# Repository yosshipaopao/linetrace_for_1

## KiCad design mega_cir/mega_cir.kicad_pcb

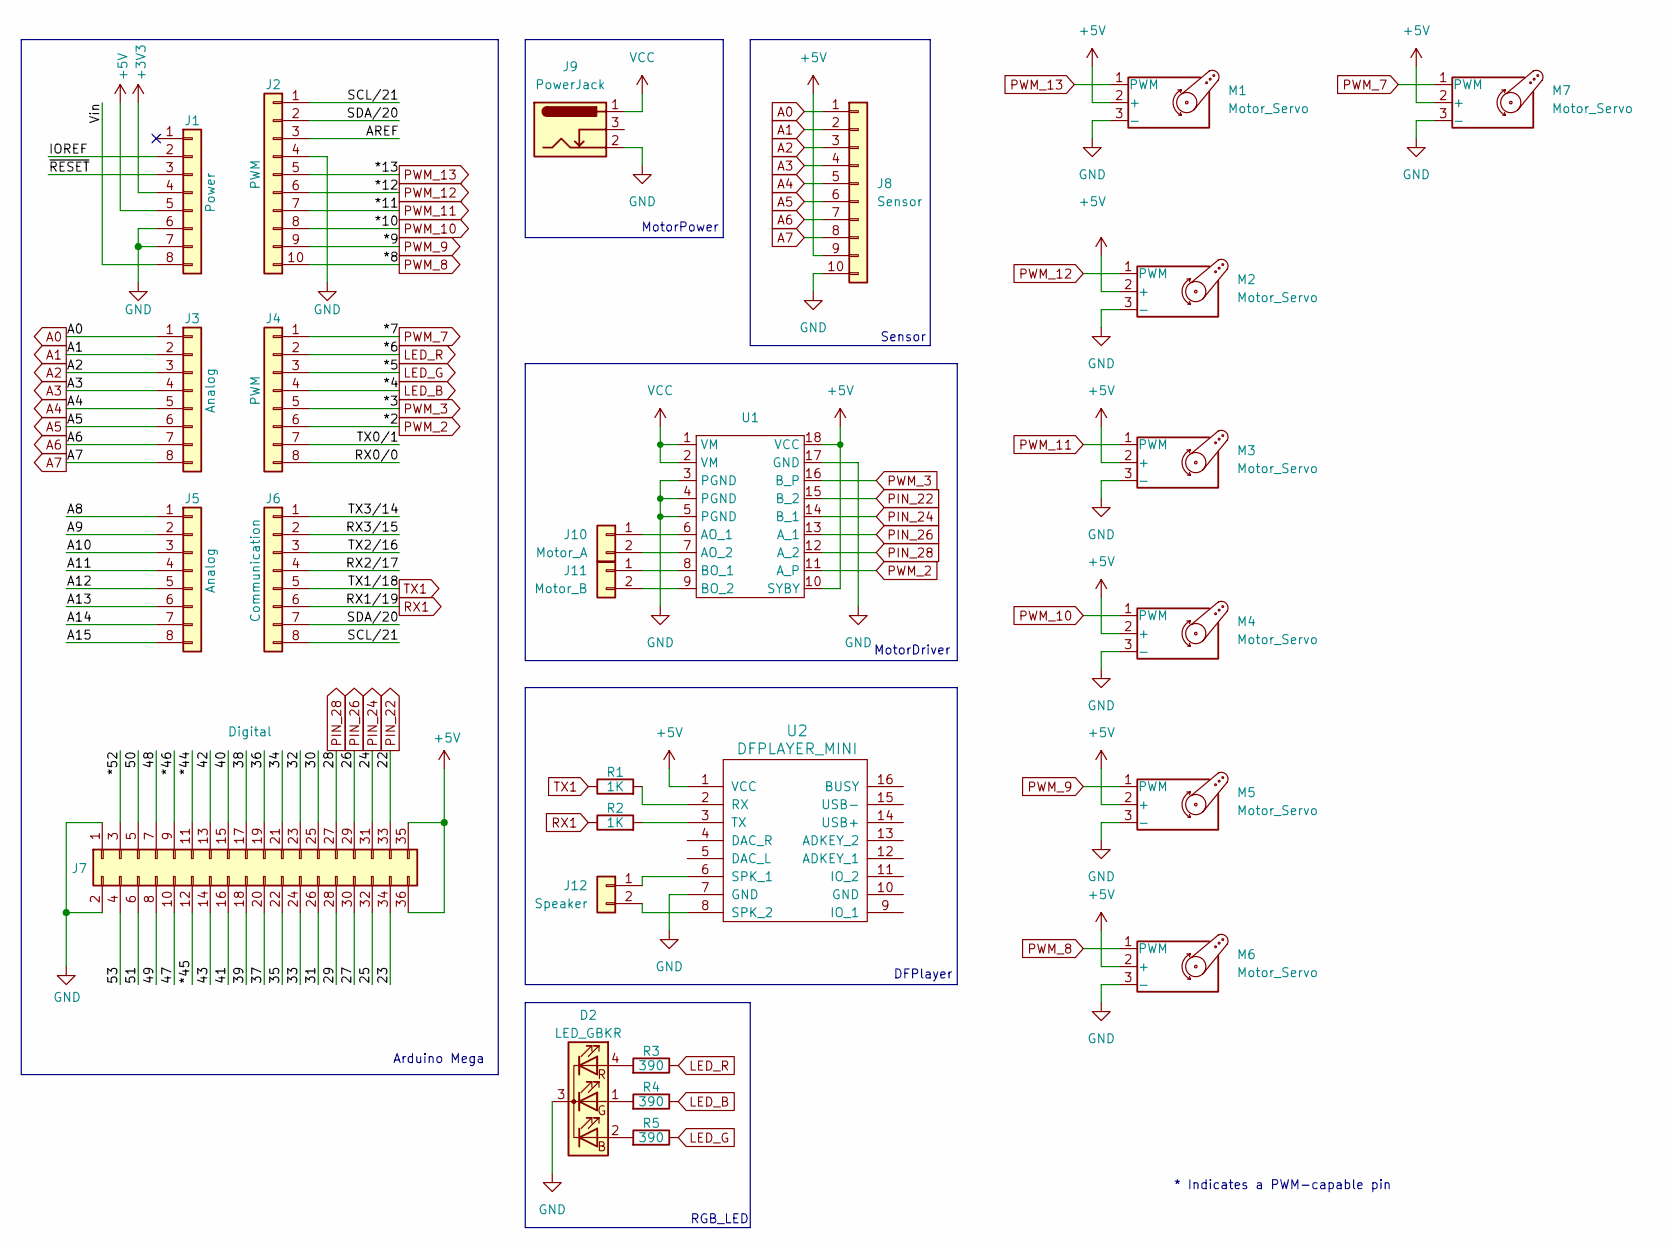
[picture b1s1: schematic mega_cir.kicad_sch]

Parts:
D2: LED_GBKR; PinHeader_1x04_P2.54mm_Vertical
J1: Power; PinSocket_1x08_P2.54mm_Vertical
J2: PWM; PinSocket_1x10_P2.54mm_Vertical
J3, J5: Analog; PinSocket_1x08_P2.54mm_Vertical
J4: PWM; PinSocket_1x08_P2.54mm_Vertical
J6: Communication; PinSocket_1x08_P2.54mm_Vertical
J7: Digital; PinSocket_2x18_P2.54mm_Vertical
J8: Sensor; PinSocket_1x10_P2.54mm_Vertical
J9: PowerJack; BarrelJack_Horizontal
J10: Motor_A; PinSocket_1x02_P2.54mm_Vertical
J11: Motor_B; PinSocket_1x02_P2.54mm_Vertical
J12: Speaker; PinSocket_1x02_P2.54mm_Vertical
M1, M2, M3, M4, M5, M6, M7: Motor_Servo; PinHeader_1x03_P2.54mm_Vertical
R1, R2: 1K; R_Axial_DIN0207_L6.3mm_D2.5mm_P7.62mm_Horizontal
R3, R4, R5: 390; R_Axial_DIN0207_L6.3mm_D2.5mm_P7.62mm_Horizontal
U1: TB6612
U2: DFPLAYER_MINI; DFPlayer_mini

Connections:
+3V3: J1.4
+5V: J1.5, J7.35, J7.36, J8.9, M1.2 (+), M2.2 (+), M3.2 (+), M4.2 (+), M5.2 (+), M6.2 (+), M7.2 (+), U1.10 (SYBY), U1.18 (VCC), U2.1 (VCC)
/23: J7.34
/25: J7.32
/27: J7.30
/29: J7.28
/30: J7.25
/31: J7.26
/32: J7.23
/33: J7.24
/34: J7.21
/35: J7.22
/36: J7.19
/37: J7.20
/38: J7.17
/39: J7.18
/40: J7.15
/41: J7.16
/42: J7.13
/43: J7.14
/47: J7.10
/48: J7.7
/49: J7.8
/50: J7.5
/51: J7.6
/53: J7.4
/*44: J7.11
/*45: J7.12
/*46: J7.9
/*52: J7.3
/A8: J5.1
/A9: J5.2
/A10: J5.3
/A11: J5.4
/A12: J5.5
/A13: J5.6
/A14: J5.7
/A15: J5.8
/AREF: J2.3
/IOREF: J1.2
/RX0/0: J4.8
/RX2/17: J6.4
/RX3/15: J6.2
/SCL/21: J2.1, J6.8
/SDA/20: J2.2, J6.7
/TX0/1: J4.7
/TX2/16: J6.3
/TX3/14: J6.1
/Vin: J1.8
/~RESET: J1.3
A0: J3.1, J8.1
A1: J3.2, J8.2
A2: J3.3, J8.3
A3: J3.4, J8.4
A4: J3.5, J8.5
A5: J3.6, J8.6
A6: J3.7, J8.7
A7: J3.8, J8.8
GND: D2.3 (K), J1.6, J1.7, J2.4, J7.1, J7.2, J8.10, J9.2, M1.3 (-), M2.3 (-), M3.3 (-), M4.3 (-), M5.3 (-), M6.3 (-), M7.3 (-), U1.3 (PGND), U1.4 (PGND), U1.5 (PGND), U1.17 (GND), U2.7 (GND)
LED_B: J4.4, R4.1
LED_G: J4.3, R5.1
LED_R: J4.2, R3.1
unnamed: D2.2 (BA), R5.2
unnamed: D2.1 (GA), R4.2
unnamed: D2.4 (RA), R3.2
unnamed: J10.1, U1.6 (AO_1)
unnamed: J10.2, U1.7 (AO_2)
unnamed: J11.1, U1.8 (BO_1)
unnamed: J11.2, U1.9 (BO_2)
unnamed: J12.1, U2.6 (SPK_1)
unnamed: J12.2, U2.8 (SPK_2)
unnamed: R1.2, U2.2 (RX)
unnamed: R2.2, U2.3 (TX)
PIN_22: J7.33, U1.15 (B_2)
PIN_24: J7.31, U1.14 (B_1)
PIN_26: J7.29, U1.13 (A_1)
PIN_28: J7.27, U1.12 (A_2)
PWM_2: J4.6, U1.11 (A_P)
PWM_3: J4.5, U1.16 (B_P)
PWM_7: J4.1, M7.1 (PWM)
PWM_8: J2.10, M6.1 (PWM)
PWM_9: J2.9, M5.1 (PWM)
PWM_10: J2.8, M4.1 (PWM)
PWM_11: J2.7, M3.1 (PWM)
PWM_12: J2.6, M2.1 (PWM)
PWM_13: J2.5, M1.1 (PWM)
RX1: J6.6, R2.1
TX1: J6.5, R1.1
VCC: J9.1, U1.1 (VM), U1.2 (VM)

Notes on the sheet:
MotorDriver
Sensor
Arduino Mega
RGB_LED
* Indicates a PWM-capable pin
DFPlayer
MotorPower

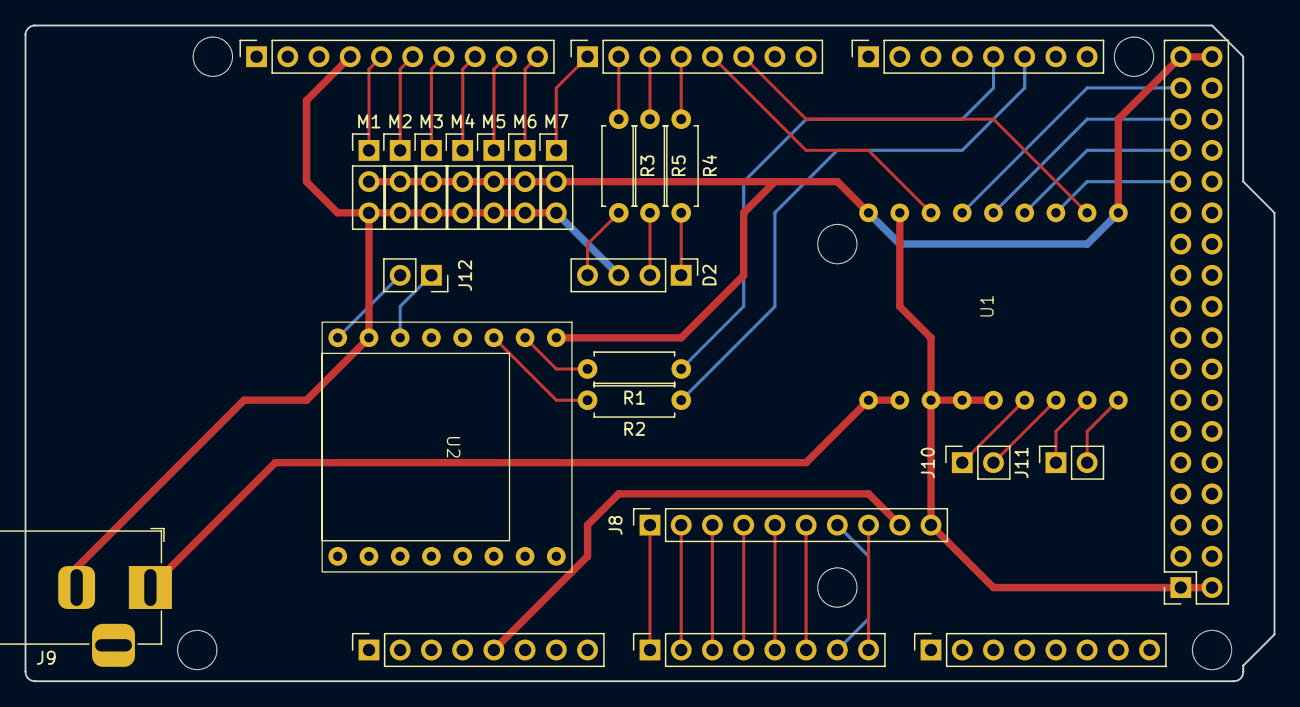
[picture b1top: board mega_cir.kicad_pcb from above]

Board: 2 copper layers, 101.6 x 53.3 mm, 33 parts (0 on the bottom side), 42 nets.

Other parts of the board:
MH1, MH2, MH3, MH4, MH5, MH6: MountingHole_3.2mm

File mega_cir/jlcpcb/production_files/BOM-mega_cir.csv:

Comment,Designator,Footprint,LCSC
LED_GBKR,D2,PinHeader_1x04_P2.54mm_Vertical,
DFPLAYER_MINI,U2,DFPlayer_mini,
~,U1,TB6612,
390,R5,R_Axial_DIN0207_L6.3mm_D2.5mm_P7.62mm_Horizontal,
390,R4,R_Axial_DIN0207_L6.3mm_D2.5mm_P7.62mm_Horizontal,
390,R3,R_Axial_DIN0207_L6.3mm_D2.5mm_P7.62mm_Horizontal,
1K,R2,R_Axial_DIN0207_L6.3mm_D2.5mm_P7.62mm_Horizontal,
1K,R1,R_Axial_DIN0207_L6.3mm_D2.5mm_P7.62mm_Horizontal,
Motor_Servo,M7,PinHeader_1x03_P2.54mm_Vertical,
Motor_Servo,M6,PinHeader_1x03_P2.54mm_Vertical,
Motor_Servo,M5,PinHeader_1x03_P2.54mm_Vertical,
Motor_Servo,M4,PinHeader_1x03_P2.54mm_Vertical,
Motor_Servo,M3,PinHeader_1x03_P2.54mm_Vertical,
Motor_Servo,M2,PinHeader_1x03_P2.54mm_Vertical,
Motor_Servo,M1,PinHeader_1x03_P2.54mm_Vertical,
Speaker,J12,PinSocket_1x02_P2.54mm_Vertical,
Motor_B,J11,PinSocket_1x02_P2.54mm_Vertical,
Motor_A,J10,PinSocket_1x02_P2.54mm_Vertical,
PowerJack,J9,BarrelJack_Horizontal,
Sensor,J8,PinSocket_1x10_P2.54mm_Vertical,
Digital,J7,PinSocket_2x18_P2.54mm_Vertical,
Power,J1,PinSocket_1x08_P2.54mm_Vertical,
Analog,J3,PinSocket_1x08_P2.54mm_Vertical,
Analog,J5,PinSocket_1x08_P2.54mm_Vertical,
PWM,J2,PinSocket_1x10_P2.54mm_Vertical,
PWM,J4,PinSocket_1x08_P2.54mm_Vertical,
Communication,J6,PinSocket_1x08_P2.54mm_Vertical,

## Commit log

2025-01-23 add unit
2025-01-28 add cir
2025-01-28 add prev code
